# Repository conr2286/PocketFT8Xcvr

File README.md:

# Pocket FT8 Revisited
A derivative of Charles Hill's Palm-Sized Pocket FT8 Transceiver

# Attribution
* Copyright (C) 2025, James R Conrad (KQ7B), conr2286 *at* gmail *dot* com
* Copyright (C) 2021, Charles Hill (W5BAA), https://github.com/Rotron/Pocket-FT8 
* Si4735 Library developed by Ricardo Caritti: https://github.com/pu2clr/SI4735
* FT8 Decoding Library by Karlis Goba (YL3JG): https://github.com/kgoba/ft8_lib
* SN74ACT244 PA by Barb (WB2CBA), https://github.com/WB2CBA/DX-FT8-FT8-MULTIBAND-TABLET-TRANSCEIVER 
* Adafruit, PJRC and many Arduino libraries copyrighted by their respective authors

# Permissive MIT License (applies to most project files)
* Copyright (c) 2018 Kārlis Goba
* Copyright (C) 2019 Ricardo Lima Caratti
* Copyright (C) 2021, Charles Hill (W5BAA)
* Copyright (C) 2024, 2025 Jim Conrad (KQ7B)

Permission is hereby granted, free of charge, to any person obtaining a copy of this software and associated documentation files (the "Software"), to deal in the Software without restriction, including without limitation the rights to use, copy, modify, merge, publish, distribute, sublicense, and/or sell copies of the Software, and to permit persons to whom the Software is furnished to do so, subject to the following conditions:

The above copyright notice and this permission notice shall be included in all copies or substantial portions of the Software.

THE SOFTWARE IS PROVIDED "AS IS", WITHOUT WARRANTY OF ANY KIND, EXPRESS OR IMPLIED, INCLUDING BUT NOT LIMITED TO THE WARRANTIES OF MERCHANTABILITY, FITNESS FOR A PARTICULAR PURPOSE AND NONINFRINGEMENT. IN NO EVENT SHALL THE AUTHORS OR COPYRIGHT HOLDERS BE LIABLE FOR ANY CLAIM, DAMAGES OR OTHER LIABILITY, WHETHER IN AN ACTION OF CONTRACT, TORT OR OTHERWISE, ARISING FROM, OUT OF OR IN CONNECTION WITH THE SOFTWARE OR THE USE OR OTHER DEALINGS IN THE SOFTWARE.

# CopyLeft GPL License (applies to the SI5351 library)
* Copyright (C) 2015-2019 Jason Milldrum and Dana H. Myers

# Features
* Single band, FT8 Tranceiver
* Designed for 160-15 meters, tested on 40m
* Small Size, 4.0 X 2.8", 4-layer board
* Powered by a single 5V USB source (e.g. portable USB power block) delivering ~375 mA
* Si4735 SSB Receiver
* TCXO stabilized Si5351 Clock
* SN74ACT244 PA delivering ~250 mW on 40M (Tnx, Barb;)
* ADIF Contact Logging to SD card
* Adafruit 320 X 480 Resistive Color Touch Screen
* Optional Adafruit Ultimate GPS-derived location and UTC date/time
* RoboOp sequences FT8 QSOs somewhat akin to wsjtx

# DSP Audio Architecture
Decoding FT8 requires significant data storage and processing speed.  To optimize program storage and processing speed so the Teensy is not over taxed, the Teensy Audio Library has been modified to allow Analog to Digital conversion to be run at the rate of 6400 samples per second. This allows audio data processing to be done at 3200 Hz. The 3200 Hz audio processing with a 2048 FTT to process the received audio for FT8 decoding yields a bin spacing of 3.125 Hz.  For Teensy 4.1, the revised sample rate requires replacement of the core AudioStream.h file with the AudioStream6400.h file in the PocketFT8FW sketch folder.

The algorithms developed by Karlis Goba use the 3.125 Hz spaced FFT bins to be screened in both frequency and time so that errors in symbol frequency and time reception can be overcome to provide really great FT8 decoding. The end spacing of the FT8 algorithms is 6.25 Hz.

# Motivation and Related Projects
In the mid-60s, the ARRL Handbook published a receiver design known as the Junior Miser's Dream offering so much with so little.  Today, Charley Hill's concept for a self-contained FT8 transceiver, ideal for portable operation, again achieves so much with so little.  The entire transceiver fits in a small enclosure, powered by a USB power brick.  Pocket FT8 Revisited is a derivative of Charley's original concept.

Unlike the uSDX and related multi-mode designs, Pocket FT8 focuses entirely on FT8.  If you need CW, SSB, etc then Pocket FT8 is not for you.

Charley and Barb have progressed with another Pocket FT8 derivative, DX FT8, at https://github.com/WB2CBA/DX-FT8-FT8-MULTIBAND-TABLET-TRANSCEIVER, most notably replacing the SI4735 with a Tayloe receiver.

# Manifest
* BenchTests:  Arduino sketches for incremental tests of the hardware
* Bibliography:  "..shoulders of giants"
* Doc:  Minimalist user manual
* Enclosure:  STLs for 3D printing a plastic case for an older version (needs update)
* Examples:  Sample JSON configuration and ADIF log files
* Extras:  Modified Teensy AudioStream6400.h header (you *need* this)
* Investigations:  Code and simulations exploring technologies for this project
* Mfg:  BOM files for assembly.  V2.00 has been built; the current BOM awaits tariff issues.
* PocketFT8XcvrFW:  The transceiver firmware sources
* PocketFT8XcvrHW:  KiCad files for the PCB
* RFFilters:  Investigations into various filter designs
* Extras:  Contains Teensy AudioStream.h modified for 6400 samples/second.  You *need* this.
* Schematics:  PDFs of hardware schematics.  V2.00 matches V2.00 BOM.
* SpectralPurity:  Results of investigations into transmitter output using V2.00 hardware.

# Versions
* V1.00 PCB gerbers and pos files submitted to PCBWay.
* V1.10 Transmitter works.  Receiver occasionally decodes FT8 messages.  See Issue #23 on github.
* V2.00 Revised PCB moves the SI5351 and MCP342x to Wire1 to avoid I2C noise (Issue #23) hampering the SI4735
* V2.10 Implements GPS, ADIF logging and the RoboOp QSO sequencer.  Uses V2.00 hardware with patch wires for GPS connector.  The GPS is optional but *strongly* recommended.
* V3.00 continues with the same firmware, but the hardware eliminates the requirement for the PPS patch wire and adds an expansion connector to break-out a few GPIO signals.  The V3.00 board fabrication awaits a satisfactory tariff solution.

# Implementationi Notes
* The receiver is based upon the SI4735 chip offering a compact, low-power approach for most HF bands  Following up on a tip from the SI4735's application notes, the chip was found to be extremely sensitive to noise from other I2C traffic on the same bus as the SI4735.  The V2.00 boards address this issue by moving the touchscreen (MCP342X) and SI5351 traffic from the Wire to the Wire1 I2C bus, isolating the SI4735 on Wire.  Likewise, the V2.00 boards pay more attention to signal routing adjacent to noise-sensitive circuitry.
* Many clock designs use a TCXO driving one of the SI5351's XTAL pins and often in conflict with the SI5351 application notes recommendations.  Many designers have commented (not of one voice;) on this approach.  Following up on a now-misplaced tip re. phase noise, this design employs a low jitter TCXO driving the SI5351's CLKIN pin.  Following up on yet another misplaced tip regarding the SI5351's phase noise when driving heavy loads, the V2.00 boards buffer the XCLK signal from the SI5351.  All this may be overkill but it was easy to implement.
* The V2.00 boards and the original Pocket FT8 project use an external MCP342x ADC to poll the touchscreen.  With a non-blocking ADC library, the Teensy 4.1 could likely use the second internal ADC but this idea has not yet been tested (it can be achieved using a patch to the V2.00 boards).  Alternative approaches include using a touchscreen controller.  These are considered for a future V4.00.
* The V1.10 LP filter lacked rejection of received signals below the operating frequency.  Spectral investigations into the found surprisingly strong signals in the 500..7000 kHz range having the potential to limit the receiver's performance.  The V2.00 board filter plugins offer a chance to explore a bandpass design to protect the receiver's front end.  Suitable bandpass filters have been modeled but not yet been tested.
* The V2.00 boards support the Adafruit Ultimate GPS Breakout board.  The firmware supports using the PPS digital interrupt signal to determine when the GPS acquires a fix; however, the V2.00 PCB requires a patch wire to connect the PPS pin to Teensy Digital Pin 2, and the GPS connector has the PPS pin in an awkward location for a ribbon cable.  This will hopefull be fixed in the V3.00 hardware when tariffs permit.  The patch is easy to solder and I strongly recommend it.

# Boards and Parts Availability
Pocket FT8 Revisited is not a kit.  If you seek a kit-like experience, check-out QRP Labs, the uSDX follow-ons, or the DX FT8 kit because Pocket FT8 construction requires some engineering skills and tools including KiCAD, the Arduino IDE, and Visual Studio Code with the PlatformIO extensions.  This project is more about homebrewing than operating.  That said, sometimes I have spare boards for one version or another.

# Building the Firmware
1. Install Arduino 2.X IDE (the BenchTests still require the Arduino IDE, sorry)
2. Using Arduino 2.X, install support for the Teensy 4.1 board
3. Install Visual Studio Code and PlatformIO
4. Using PlatformIO, install support for the Teensy 4.1 platform
5. Using PlatformIO, install support for the required libraries (documented in the PocketFT8XcvrFW folder)
6. Copy Extras/AudioStream6400.h into
 .../Library/Arduino15/packages/teensy/hardware/avr/1.59.0/cores/teens4 asArduinoStream.h --- This file redefines AUDIO_SAMPLE_RATE_EXACT enabling Teensy 4.1 to operate the audio stream at 6400 samples/second (required).  You absolutely *must* do this; PocketFT8XcvrFW.cpp will not execute if you forget.
7. Build the firmware with PlatformIO.  The project src files build without warnings; library files... not so much.

# Hardware Notes
Pocket FT8 Revisited was designed with KiCAD, and the V2.00 PCBs were fabbed and the SMD assembled by PCBWay.  There are two boards, the main board (PocketFT8XcvrHW) and a daughter board for the filter (RFFilters).  I used the 5Pole40MLPFilter in the SpectralPurity test.  The V3.00 boards are designed and checked but await a satisfactory tariff solution for fabrication and assembly.

# Building the Hardware
1. Attach the Teensy 4.1 MPU to the board using *low profile* headers.
2. Attach the Adafruit resistive 320x480 touchscreen with high profile headers (so the display clears the MPU)
3. Construct a suitable filter (e.g. 5-pole Chebyshev) for your chosen band of operation and solder it into the FL1 spot.  The RFFilters folder contains a KiCAD design for the filter daughter board.
4. Hand solder SMD CR2032 battery holder to reverse side of PCB and install battery (before powering-up the Teensy).  T
5. Hand solder THT red XMIT LED
6. Wind THT T1 (10T bifilar #26 on FT37-43 core) and install
7. Install right angle header for GPS.  Hand solder a PPS patch wire from the GPS connector to the MCU as described above.
8. Hand solder the SMD SMA antenna socket to the board
9. Smoke test with wall wart USB supply (not your expensive computer;)
10. Build and execute each of the BenchTests (with Arduino IDE 2.00) in numerical order to individually check-out the circuit subsystems.

# Putting Pocket FT8 Revisited On-the-Air
1. Create an SD file, CONFIG.JSON, to configure the Pocket FT8 for your station (see the sample file in Examples).  The required parameters are, callsign and frequency.  If you don't have a GPS, you'll also need location.  Install the SD card in Teensy (*not* in the Adafruit display which also has an SD slot).
2. If you are using a GPS, connect it now.
3. Connect an antenna 
4. Connect your host computer and load your firmware

# Usage
## CONFIG.JSON
During setup(), the rig reads the config.json file, if available, from the Teensy SD card.  The SD card and configuration file are required to enable the transmitter.  See the example config file in the Examples folder.  The important configuration parameters include:
* callsign      Station callsign.  *Required* to enable the transmitter.
* frequency     Operating frequency in kHz (default is 7074).
* locator       Four letter Maidenhead grid square (Required if no GPS).
* enableAVC     Enable/disable SI4735 AVC (default is enabled).
* qsoTimeout    Seconds the QSO Sequencer will retransmit a msg without receiving a usable response from remote station (default is 180)

## GPS
If available, the rig will use the current UTC date, time and location (Maidenhead grid square) from an attached GPS.  The V2.00 hardware requires a patch wire to connect the GPS PPS connector pin to Teensy digital pin 2.  The firmware monitors PPS interrupts and begins using the UTC time and location only when/if the GPS acquires a satellite fix.  
Without a GPS fix, the firmware uses the date/time from the battery-backed Teensy Real Time Clock (RTC) and displays that date/time in yellow.  After a fix is obtained, the date/time displays in green.  The GPS is not required but *greatly* facilitates UTC logging and accurate synchronization with FT8 timeslots.

## Logging
Pocket FT8 logs successful contacts to an ADIF file on the Teensy SD disk.  The date/time are recorded in UTC if the rig has acquired a GPS fix.  If the rig has never had a GPS fix, the date/time come from the boot loader and the computer that installed the firmware --- that may work for FT8 but the UTC date/time will be incorrect in the ADIF log.  You really do want the GPS.  The logging software considers a contact successful when the rig obtains the remote station's callsign and signal report (yes, that's a little more severe than required by ARRL's LoTW).  Without a GPS, the grid locator can be obtained from the configuration file.

## Robo-Op
Pocket FT8 firmware includes a "RoboOp" "sequencer somewhat akin (or ajar...;) to those used in wsjtx and DX FT8.  The sequencer conducts a standard FT8 QSO initiated with your station's CQ, or with your reply to a station calling CQ.  The sequencer automagically coordinates its transmissions with those of the remote station to avoid "doubling" (transmitting in the same timeslot as the remote transmission).  In most cases, the sequencer prepares a reply during the FT8 "dwell" time (between timeslots) and can transmit in the very next timeslot.  If not... well... it will wait for an appriopriate even/odd timeslot.
The sequencer is implemented as a giant state machine that attempts to make the best of difficult conditions/responses to complete a troubled QSO.  The sequencer has a configurable QSO Timeout feature to abort a run-on QSO (including CQ) arising from QRM, QRN, or a QRT/QLF remote station.  As with most large state machines... the code is difficult to follow, but is mitigated with an abundance of comments that attempt to explain what's happening in the various event handlers and their actions.

## CQ Button
The CQ button directs RoboOp to begin calling CQ in the next FT8 timeslot.  RoboOp will continue calling CQ until either a response is received, a timeout occurs, the operator toggles the CQ button, or clicks the ABort button.

## TU Button
The TUne button transmits a dead carrier at the CONFIG.JSON specified operating frequency.  Toggling the TUne button or clicking ABort drops the carrier.

## AB Button
The ABort button aborts a transmission in-progress.

## TX Button
The TX button directs RoboOp to respond to the first received CQ message.  Unless CONFIG.JSON has configured otherwise, RoboOp ignores recent duplicates already in the log.  Toggling the TX button or the completion of a QSO disables the TX mode auto-responses.

## M0, M1 and M2 Buttons
These buttons transmit a free-text FT8 message specified in CONFIG.JSON.

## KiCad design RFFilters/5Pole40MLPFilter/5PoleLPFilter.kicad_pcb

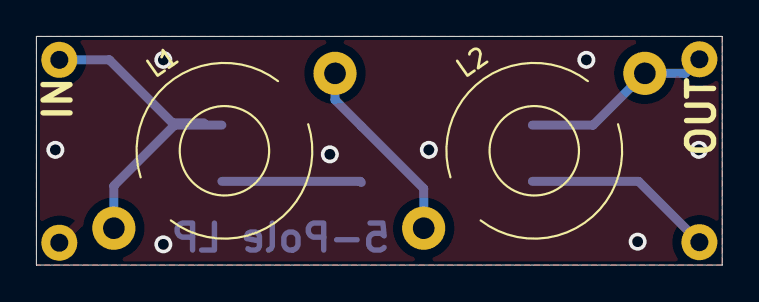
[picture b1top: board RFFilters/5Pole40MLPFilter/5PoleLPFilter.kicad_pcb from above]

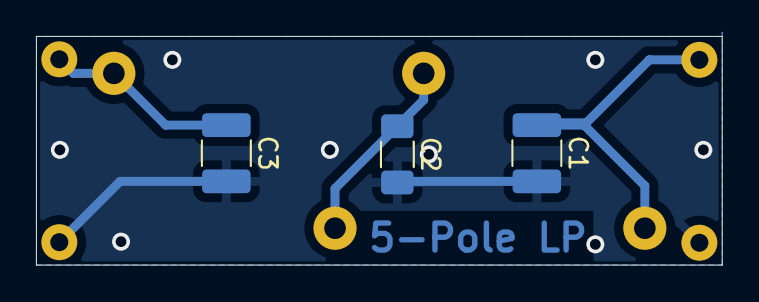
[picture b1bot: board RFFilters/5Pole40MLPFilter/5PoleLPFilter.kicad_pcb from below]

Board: 2 copper layers, 38.1 x 12.7 mm, 6 parts (3 on the bottom side), 2 nets.

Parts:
C1, C3: 1000pF; C_1210_3225Metric_Pad1.33x2.70mm_HandSolder
C2: 1300pf; C_1206_3216Metric_Pad1.33x1.80mm_HandSolder
J1: FilterConn02
L1, L2: 1.2uH; L_Toroid_Horizontal_D9.5mm_P15.00mm_Diameter10-5mm_Amidon-T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

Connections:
/Mid: C2.1, L1.2, L2.1
GND: C1.2, C2.2, C3.2, J1.2

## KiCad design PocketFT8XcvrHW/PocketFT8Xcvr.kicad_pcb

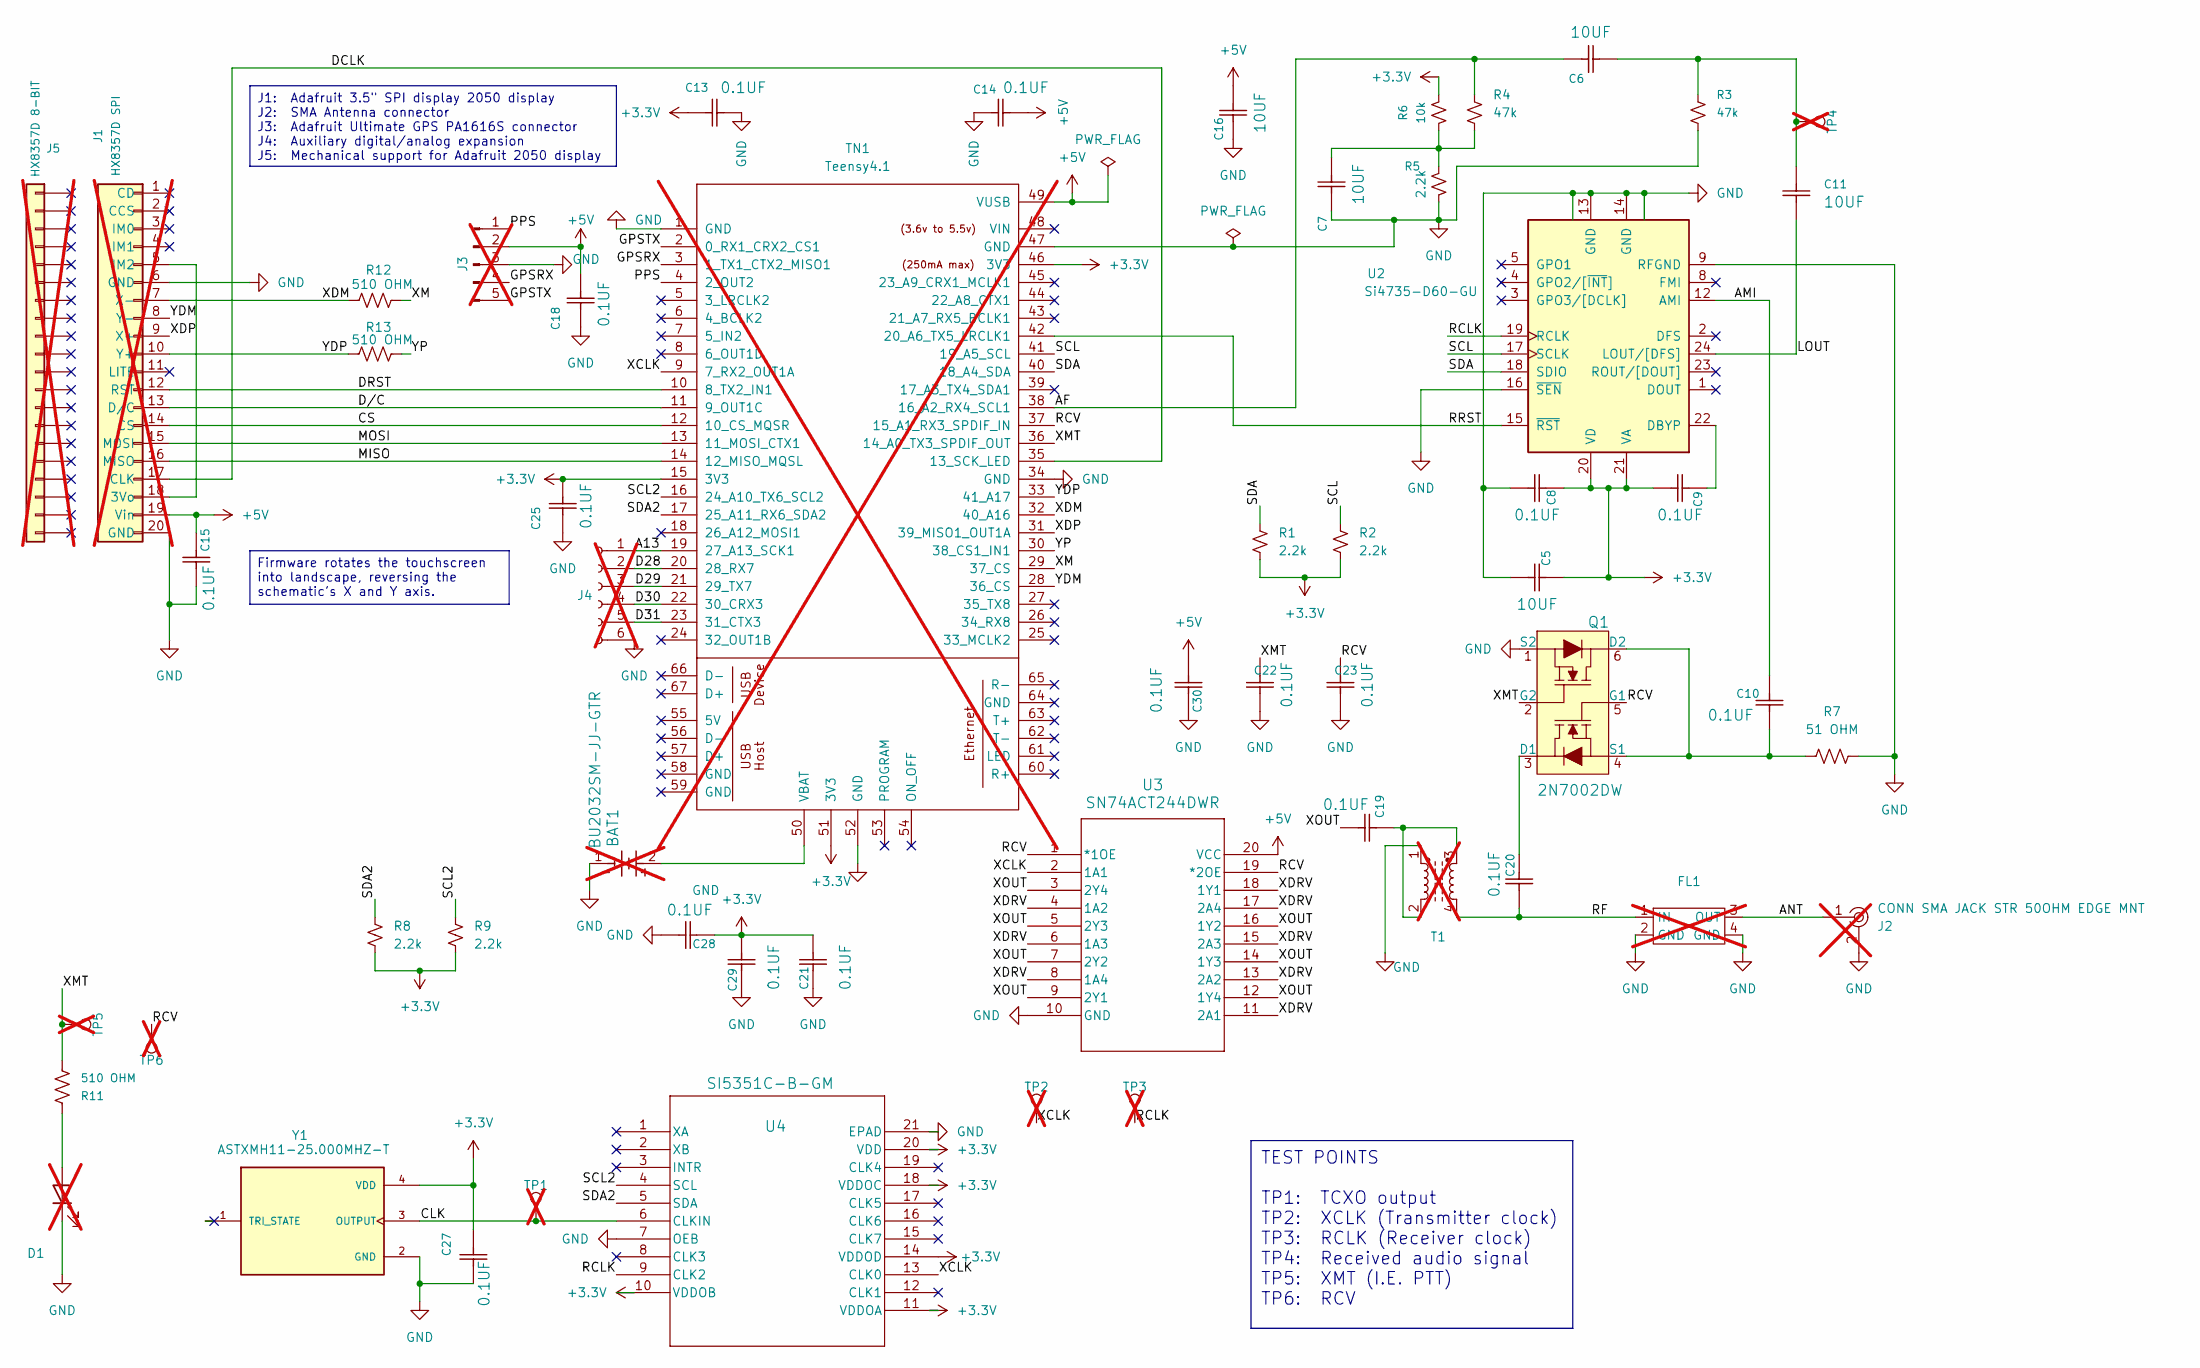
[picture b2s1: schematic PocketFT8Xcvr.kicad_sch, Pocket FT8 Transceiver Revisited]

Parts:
BAT1: BU2032SM-JJ-GTR; BU2032SM-JJ-GTR_MPD; Mfg Part # BU2032SM-JJ-GTR; not fitted
C5: 10UF; C_0805_2012Metric; Voltage 16V; Tolerance 10%; Mfg Part # C0805C106K4PAC7800
C6, C7, C11, C16: 10UF; C_0805_2012Metric; Voltage 6.3V; Tolerance 20%; Mfg Part # C0805C106K4PAC7800
C8, C9, C10, C13, C14, C15, C18, C19, C20, C21, C22, C23, C25, C27, C28, C29, C30: 0.1UF; C_0603_1608Metric; Voltage 16V; Tolerance 10%; Mfg Part # C0603C104K4RACTU
D1: XMIT; LED_D5.0mm; not fitted
FL1: PluginFilter; not fitted
J1: HX8357D SPI; PinHeader_1x20_P2.54mm_Vertical; not fitted
J2: CONN SMA JACK STR 50OHM EDGE MNT; RF_SMA_BoardEdge_142-0701-801; MPN 732511153; Digi-Key_PN J502-ND; not fitted
J3: B5B-XH-A_LF__SN_; PinHeader_1x5_P2.5mm_Drill1.1mm; MPN B5B-XH-A(LF)(SN); Digi-Key_PN 455-2270-ND; not fitted
J4: Conn_01x06_Socket; 1x06; not fitted
J5: HX8357D 8-BIT; PinHeader_1x20_P2.54mm_Vertical; not fitted
Q1: 2N7002DW; SOT-363; Mfg Part # 2N7002DW; Digi-Key_PN 2N7002DWCT-ND
R1, R2, R5, R8, R9: 2.2k; R_0603_1608Metric; Mfg Part # RC0603JR-132K2L
R3, R4: 47k; R_0603_1608Metric; Mfg Part # RC0603JR-0747KL; LCSC Part # C127447
R6: 10k; R_0603_1608Metric; Mfg Part # AF0603JR-0710KL; LCSC Part # C99198
R7: 51 OHM; R_0603_1608Metric; Mfg Part # RC0603JR-0751RL
R11, R12, R13: 510 OHM; R_0603_1608Metric; MFG PART # RC0603JR-07510RL
T1: L_Ferrite_Coupled; L_Toroid_Vertical_BIFILAR; not fitted
TN1: Teensy4.1; Teensy41; not fitted
TP1, TP2, TP3, TP4, TP5, TP6: PTH; 1x01; not fitted
U2: Si4735-D60-GU; SSOP-24_3.9x8.7mm_P0.635mm; Mfg Part # SI4735-D60-GU
U3: SN74ACT244DWR; DW20; Mfg Part # SN74ACT244DWR
U4: SI5351C-B-GM; QFN20_4X4_SKY; Mfg Part # SI5351C-B-GM
Y1: ASTXMH11-25.000MHZ-T; XTAL_ASTX-H11-25.000MHZ-T; PARTREV 05.13.15

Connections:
+3.3V: C5.2, C8.2, C9.1, C13.1, C21.2, C25.1, C27.2, C28.1, C29.2, R1.1, R2.1, R6.1, R8.1, R9.1, TN1.15 (3V3), TN1.46 (3V3), TN1.51 (3V3), U2.20 (VD), U2.21 (VA), U4.10 (VDDOB), U4.11 (VDDOA), U4.14 (VDDOD), U4.18 (VDDOC), U4.20 (VDD), Y1.4 (VDD)
+5V: C14.2, C15.2, C16.2, C18.2, C30.2, J1.19 (Vin), J3.2, TN1.49 (VUSB), U3.20 (VCC)
/A13: J4.1, TN1.19 (27_A13_SCK1)
/AF: C6.2, R4.1, TN1.38 (16_A2_RX4_SCL1)
/AMI: C10.2, U2.12 (AMI)
/ANT: FL1.3 (OUT), J2.1
/CLK: TP1.1, U4.6 (CLKIN), Y1.3 (OUTPUT)
/CS: J1.14 (CS), TN1.12 (10_CS_MQSR)
/D28: J4.2, TN1.20 (28_RX7)
/D29: J4.3, TN1.21 (29_TX7)
/D30: J4.4, TN1.22 (30_CRX3)
/D31: J4.5, TN1.23 (31_CTX3)
/DCLK: J1.17 (CLK), TN1.35 (13_SCK_LED)
/DRST: J1.12 (RST), TN1.10 (8_TX2_IN1)
/D/C: J1.13 (D/C), TN1.11 (9_OUT1C)
/GPSRX: J3.4, TN1.3 (1_TX1_CTX2_MISO1)
/GPSTX: J3.5, TN1.2 (0_RX1_CRX2_CS1)
/LOUT: C11.1, U2.24 (LOUT/[DFS])
/MISO: J1.16 (MISO), TN1.14 (12_MISO_MQSL)
/MOSI: J1.15 (MOSI), TN1.13 (11_MOSI_CTX1)
/PPS: J3.1, TN1.4 (2_OUT2)
/RCLK: TP3.1, U2.19 (RCLK), U4.9 (CLK2)
/RCV: C23.2, Q1.5 (G1), TN1.37 (15_A1_RX3_SPDIF_IN), TP6.1, U3.1 (*1OE), U3.19 (*2OE)
/RF: C20.2, FL1.1 (IN), T1.4
/RRST: TN1.42 (20_A6_TX5_LRCLK1), U2.15 (~RST)
/SCL: R2.2, TN1.41 (19_A5_SCL), U2.17 (SCLK)
/SCL2: R9.2, TN1.16 (24_A10_TX6_SCL2), U4.4 (SCL)
/SDA: R1.2, TN1.40 (18_A4_SDA), U2.18 (SDIO)
/SDA2: R8.2, TN1.17 (25_A11_RX6_SDA2), U4.5 (SDA)
/XCLK: TN1.9 (7_RX2_OUT1A), TP2.1, U3.2 (1A1), U4.13 (CLK0)
/XDM: J1.7 (X-), R12.1, TN1.32 (40_A16)
/XDP: J1.9 (X+), TN1.31 (39_MISO1_OUT1A)
/XDRV: U3.4 (1A2), U3.6 (1A3), U3.8 (1A4), U3.11 (2A1), U3.13 (2A2), U3.15 (2A3), U3.17 (2A4), U3.18 (1Y1)
/XM: R12.2, TN1.29 (37_CS)
/XMT: C22.2, Q1.2 (G2), R11.2, TN1.36 (14_A0_TX3_SPDIF_OUT), TP5.1
/XOUT: C19.1, U3.3 (2Y4), U3.5 (2Y3), U3.7 (2Y2), U3.9 (2Y1), U3.12 (1Y4), U3.14 (1Y3), U3.16 (1Y2)
/YDM: J1.8 (Y-), TN1.28 (36_CS)
/YDP: J1.10 (Y+), R13.1, TN1.33 (41_A17)
/YP: R13.2, TN1.30 (38_CS1_IN1)
GND: BAT1.1, C5.1, C7.1, C8.1, C13.2, C14.1, C15.1, C16.1, C18.1, C21.1, C22.1, C23.1, C25.2, C27.1, C28.2, C29.1, C30.1, D1.1 (K), FL1.2 (GND), FL1.4 (GND), J1.6 (GND), J1.20 (GND), J2.2, J3.3, J4.6, Q1.1 (S2), R3.2, R5.2, R7.1, T1.1, TN1.1 (GND), TN1.34 (GND), TN1.47 (GND), TN1.52 (GND), U2.9 (RFGND), U2.10 (NC), U2.11 (NC), U2.13 (GND), U2.14 (GND), U2.16 (~SEN), U3.10 (GND), U4.7 (OEB), U4.21 (EPAD), Y1.2 (GND)
unnamed: C7.2, R4.2, R5.1, R6.2
unnamed: C6.1, C11.2, R3.1, TP4.1
unnamed: C19.2, T1.2, T1.3
unnamed: D1.2 (A), R11.1
unnamed: J1.5 (IM2), J1.18 (3Vo)
unnamed: C20.1, Q1.3 (D1)
unnamed: C10.1, Q1.4 (S1), Q1.6 (D2), R7.2
unnamed: BAT1.2, TN1.50 (VBAT)
unnamed: C9.2, U2.22 (DBYP)

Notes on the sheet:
TEST POINTS TP1: TCXO output TP2: XCLK (Transmitter clock) TP3: RCLK (Receiver clock) TP4: Received audio signal TP5: XMT (I.E. PTT) TP6: RCV
Firmware rotates the touchscreen into landscape, reversing the schematic's X and Y axis.
J1: Adafruit 3.5" SPI display 2050 display J2: SMA Antenna connector J3: Adafruit Ultimate GPS PA1616S connector J4: Auxiliary digital/analog expansion J5: Mechanical support for Adafruit 2050 display

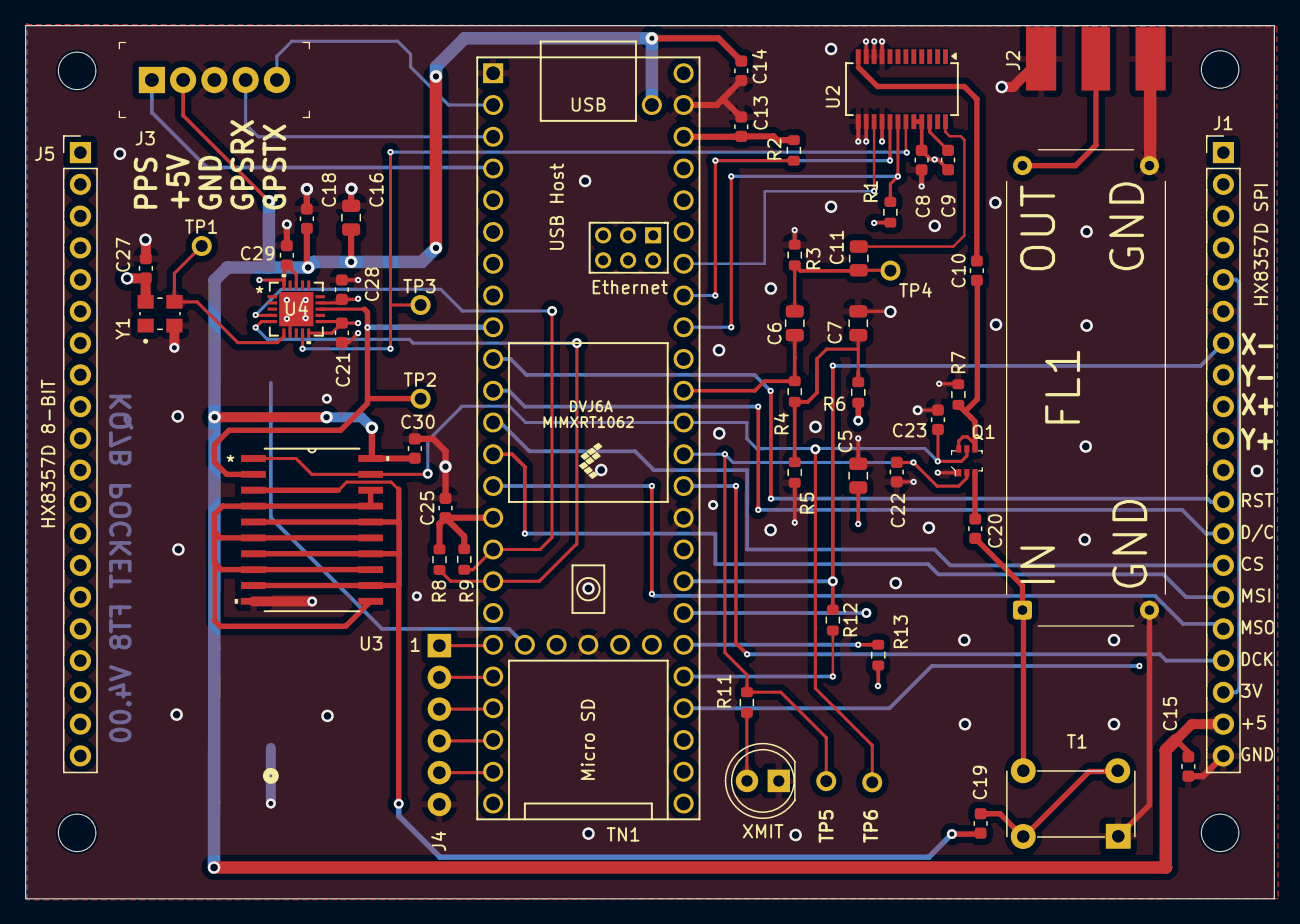
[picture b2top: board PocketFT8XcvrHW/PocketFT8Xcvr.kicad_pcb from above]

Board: 4 copper layers, 99.9 x 69.9 mm, 55 parts (1 on the bottom side), 49 nets.

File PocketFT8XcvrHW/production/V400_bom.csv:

Designator,Footprint,Quantity,Value,LCSC Part #
"C10, C13, C14, C15, C18, C19, C20, C21, C22, C23, C25, C27, C28, C29, C30, C8, C9",0603,17,0.1UF,
"C11, C16, C5, C6, C7",0805,5,10UF,
Q1,SOT-363,1,2N7002DW,
"R1, R2, R8, R9",0603,4,2.0K,
R11,0603,1,510 Ohm,
"R12, R13",0603,2,510,
"R3, R4",0603,2,47K,
R5,0603,1,2.2K,
R6,0603,1,10k,
R7,0603,1,51 OHM,
U2,SSOP-24_3.9x8.7mm_P0.635mm,1,Si4735-D60-GU,
U3,DW20,1,SN74ACT244DWR,
U4,QFN20_4X4_SKY,1,SI5351C-B-GM,
Y1,XTAL_ASTX-H11-25.000MHZ-T,1,ASTXMH11-25.000MHZ-T,

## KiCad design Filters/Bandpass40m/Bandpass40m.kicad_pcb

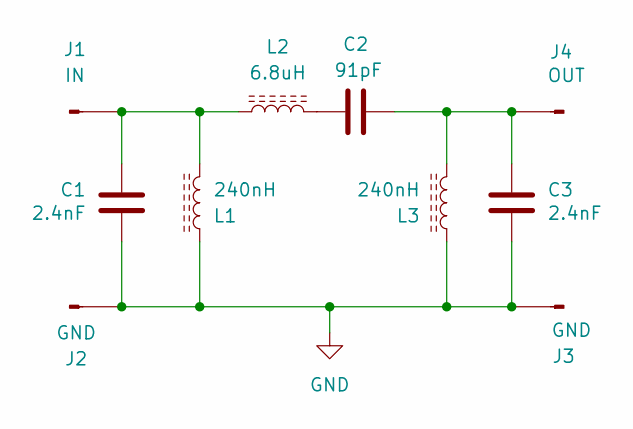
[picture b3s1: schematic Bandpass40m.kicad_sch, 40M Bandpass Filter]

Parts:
C1, C3: 2.4nF; C_0603_1608Metric_Pad1.08x0.95mm_HandSolder; MPN GCM1885C1H242FA16J
C2: 91pF; C_0603_1608Metric_Pad1.08x0.95mm_HandSolder; MPN GCM1885C2A910FA16D
J1: IN; PinHeader_1x01_P2.00mm_Vertical
J2, J3: GND; PinHeader_1x01_P2.00mm_Vertical
J4: OUT; PinHeader_1x01_P2.00mm_Vertical
L1, L3: 240nH; Inductor_THT_Horizontal_T37
L2: 6.8uH; Inductor_THT_Horizontal_T37

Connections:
GND: C1.2, C3.2, J2.1, J3.1, L1.2, L3.1
unnamed: C2.1, L2.2
unnamed: C1.1, J1.1, L1.1, L2.1
unnamed: C2.2, C3.1, J4.1, L3.2

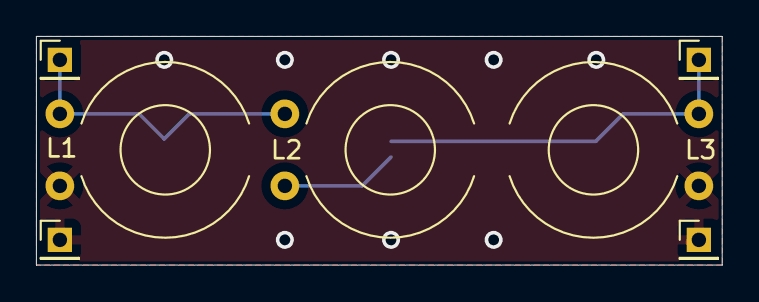
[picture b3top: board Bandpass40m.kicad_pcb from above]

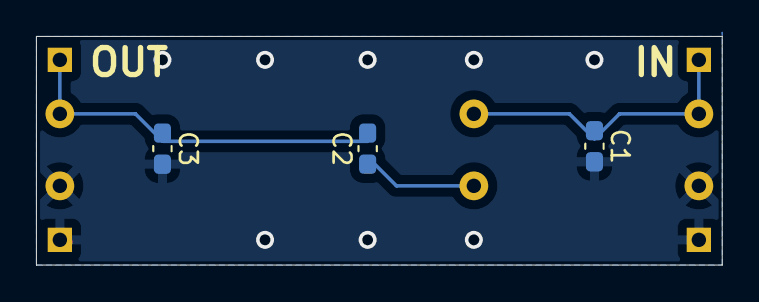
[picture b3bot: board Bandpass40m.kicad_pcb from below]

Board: 2 copper layers, 38.1 x 12.7 mm, 10 parts (3 on the bottom side), 4 nets.

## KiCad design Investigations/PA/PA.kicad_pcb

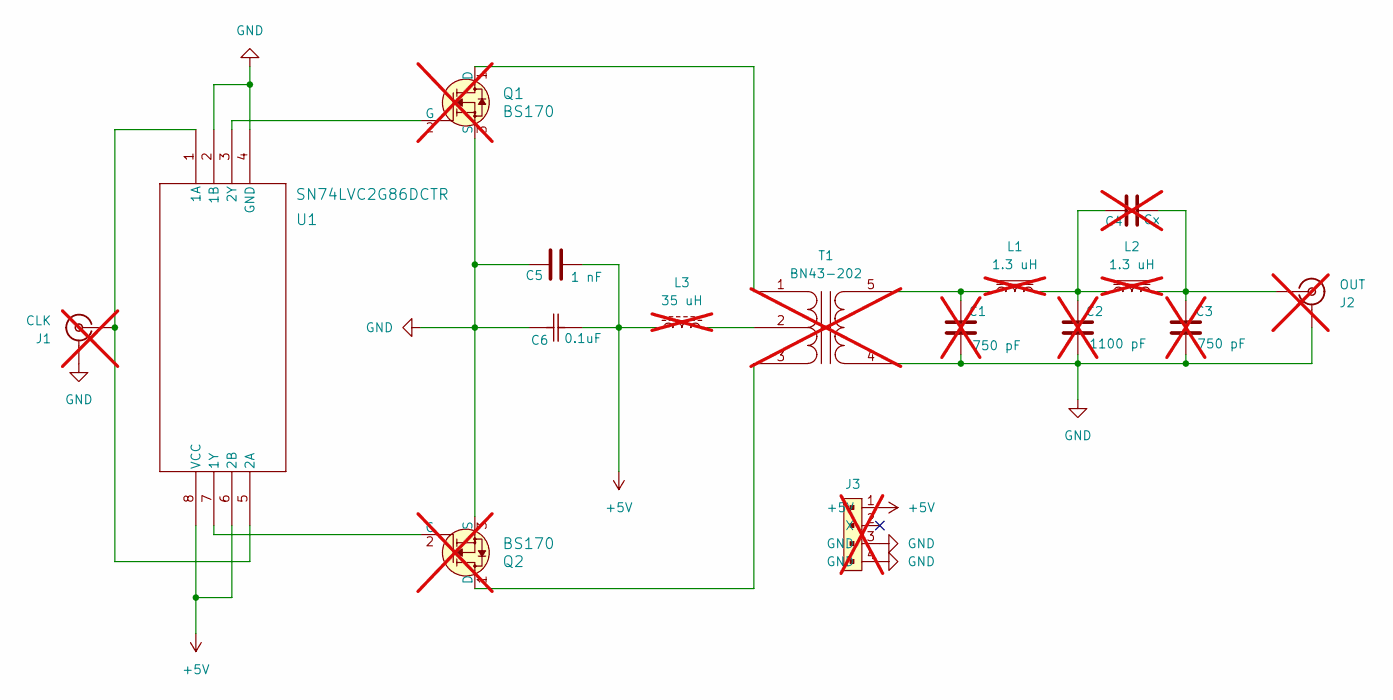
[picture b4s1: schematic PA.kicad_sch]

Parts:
C1, C3: 750 pF; 1210; Voltage 1kV; Tolerance 100%; not fitted
C2: 1100 pF; 1210; Voltage 1kV; Tolerance 100%; not fitted
C4: Cx; 1210; Voltage 1kV; Tolerance 100%; not fitted
C5: 1 nF; 1210; Voltage 50V; Tolerance 5%
C6: 0.1uF; 1210; Voltage 50V; Tolerance 5%; Mfg Part # C1210C104J5GAC7800
J1: CLK; SMA_Edge; not fitted
J2: OUT; SMA_Edge; not fitted
J3: 0022232041; PinHeader_1x4_P2.54mm_Drill1.02mm; MPN 0022232041; Digi-Key_PN WM4202-ND; not fitted
L1, L2: 1.3 uH; L_Toroid_Vertical_L13.0mm_W6.5mm_P5.60mm; not fitted
L3: 35 uH; L_Toroid_Vertical_L14.0mm_W5.6mm_P5.30mm_Bourns_5700; not fitted
Q1, Q2: BS170; TO-92-3; MPN BS170; Digi-Key_PN BS170-ND; not fitted
T1: BN43-202; not fitted
U1: SN74LVC2G86DCTR; DCT8_TEX

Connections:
+5V: C5.2, C6.1, J3.1 (+5V), L3.1, U1.6 (2B), U1.8 (VCC)
GND: C1.2, C2.2, C3.2, C5.1, C6.2, J1.2 (Ext), J2.2 (Ext), J3.3 (GND), J3.4 (GND), Q1.3 (S), Q2.3 (S), T1.4 (S1), U1.2 (1B), U1.4 (GND)
unnamed: C2.1, C4.1, L1.2, L2.1
unnamed: J1.1 (In), U1.1 (1A), U1.5 (2A)
unnamed: C3.1, C4.2, J2.1 (out), L2.2
unnamed: Q1.1 (D), T1.1 (PR1)
unnamed: Q1.2 (G), U1.3 (2Y)
unnamed: Q2.1 (D), T1.3 (PR2)
unnamed: Q2.2 (G), U1.7 (1Y)
unnamed: L3.2, T1.2 (PM)
unnamed: C1.1, L1.1, T1.5 (S2)

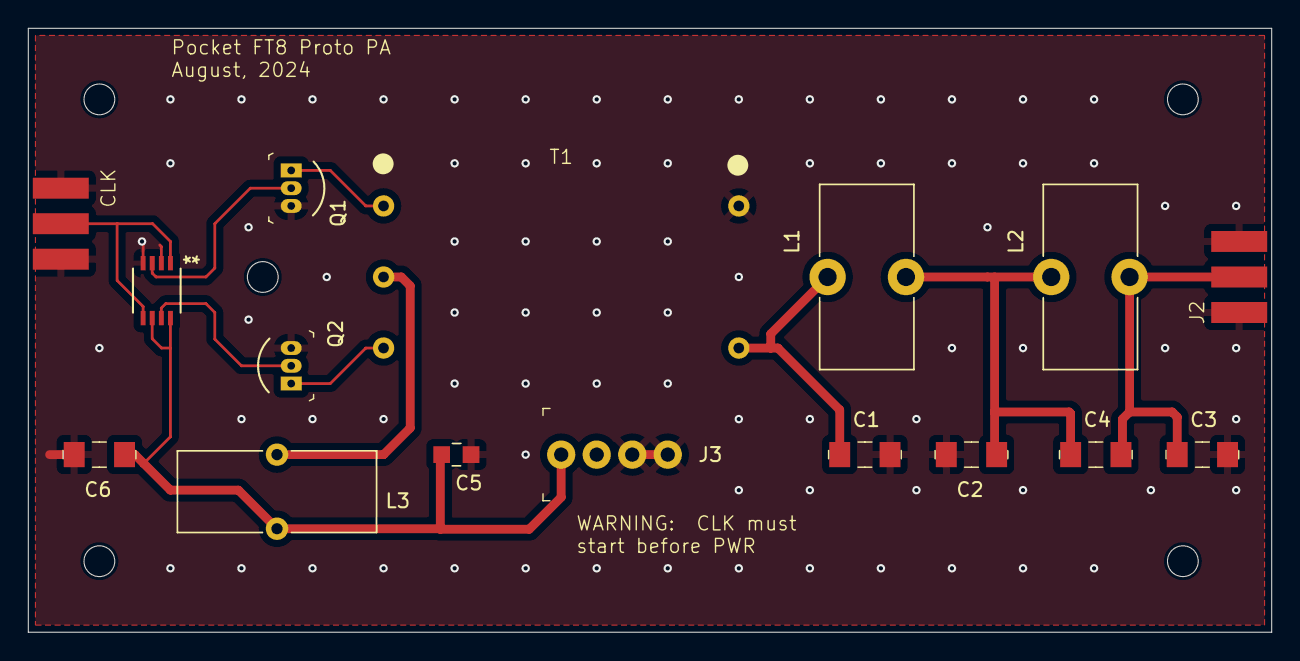
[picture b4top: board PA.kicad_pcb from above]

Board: 2 copper layers, 88.9 x 43.2 mm, 16 parts (0 on the bottom side), 11 nets.

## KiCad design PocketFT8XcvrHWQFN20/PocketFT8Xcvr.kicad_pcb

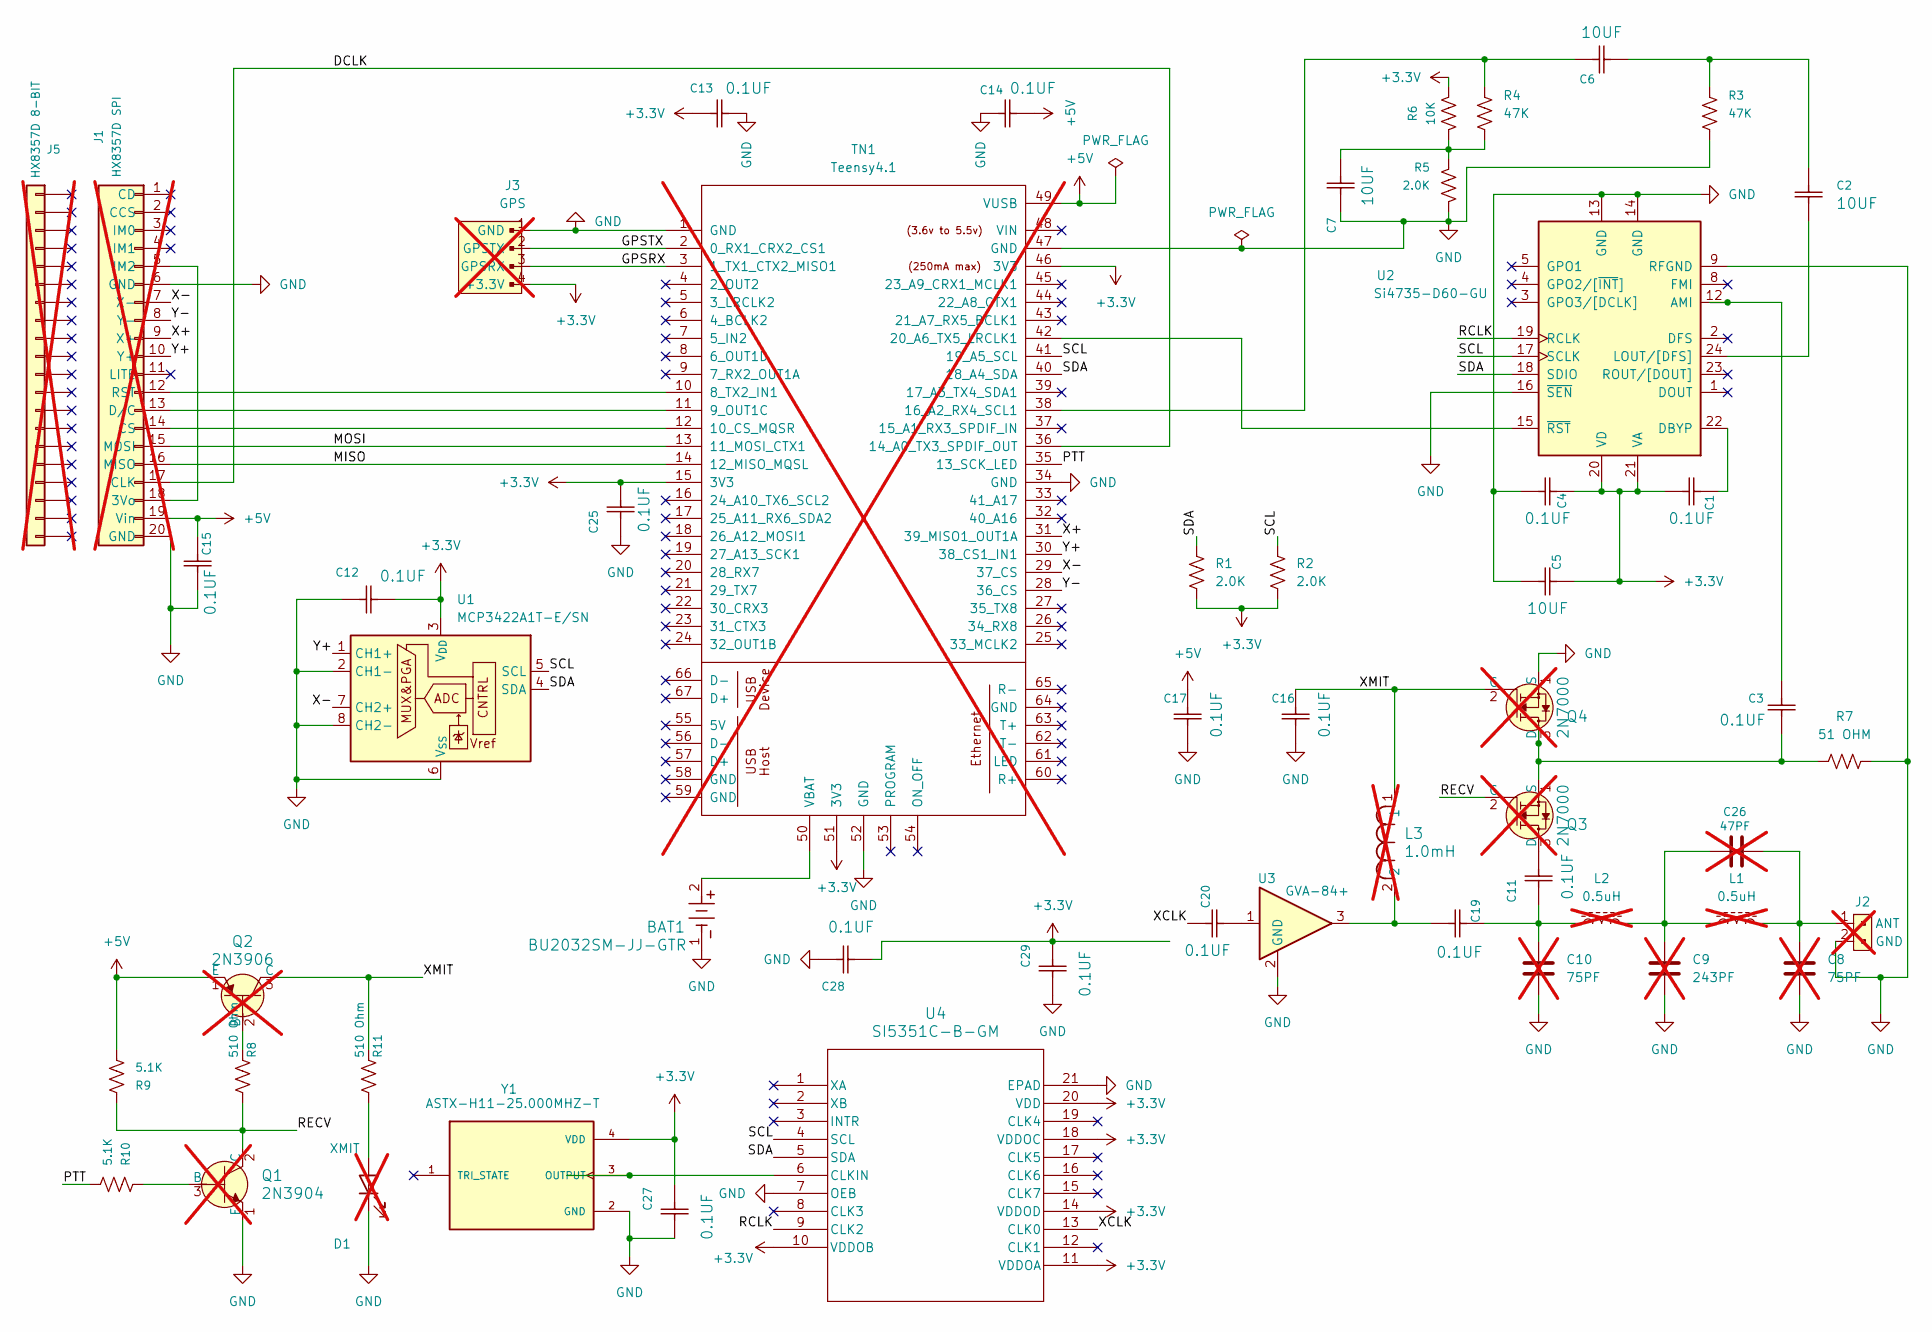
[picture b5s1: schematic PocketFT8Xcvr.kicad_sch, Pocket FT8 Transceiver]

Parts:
BAT1: BU2032SM-JJ-GTR; BU2032SM-JJ-GTR_MPD; Mfg Part # BU2032SM-JJ-GTR
C1, C3, C4, C11, C12, C13, C14, C15, C16, C17, C19, C20, C25, C27, C28, C29: 0.1UF; C_0603_1608Metric; Voltage 16V; Tolerance 10%; Mfg Part # C0603C104K4RAC7867
C2, C6, C7: 10UF; C_0805_2012Metric; Voltage 6.3V; Tolerance 20%; Mfg Part # C0805C106K4PAC7800
C5: 10UF; C_0805_2012Metric; Voltage 16V; Tolerance 10%; Mfg Part # C0805C106K4PAC7800
C8, C10: 75PF; C_0805_2012Metric; not fitted
C9: 243PF; C_0805_2012Metric; not fitted
C26: 47PF; C_0805_2012Metric; Voltage 100v; Tolerance 1%; not fitted
D1: XMIT; LED_D5.0mm; not fitted
J1: HX8357D SPI; PinHeader_1x20_P2.54mm_Vertical; not fitted
J2: 22-23-2021; PinHeader_1x2_P2.54mm_Drill1.02mm; MPN 22-23-2021; Digi-Key_PN WM4200-ND; not fitted
J3: GPS; PinHeader_1x4_P2.54mm_Drill1.02mm; MPN 0022232041; Digi-Key_PN WM4202-ND; not fitted
J5: HX8357D 8-BIT; PinHeader_1x20_P2.54mm_Vertical; not fitted
L1, L2: 0.5uH; L_Toroid_Vertical_L10.0mm_W5.0mm_P5.08mm; not fitted
L3: 1.0mH; IND_BOURNS_RLB9012; Mfg Part # RLB9012-102KL; Digi-Key_PN RLB9012-102KL-N; not fitted
Q1: 2N3904; TO-92-3; Mfg Part # 2N3904; Digi-Key_PN 2N3904CS-ND; not fitted
Q2: 2N3906; TO-92-3; Mfg Part # 2N3906; Digi-Key_PN 2N3906CS-ND; not fitted
Q3: 2N7000; TO-92-3; Mfg Part # 2N7000; Digi-Key_PN 2N7000FS-ND; not fitted
Q4: 2N7000; TO-92-3; MPN 2N7000; Digi-Key_PN 2N7000FS-ND; not fitted
R1, R2, R5: 2.0K; R_0603_1608Metric; Mfg Part # RC0603JR-072KL
R3, R4: 47K; R_0603_1608Metric; Mfg Part # RC0603JR-0747KL
R6: 10K; R_0603_1608Metric; Mfg Part # RC0603JR-0710KL
R7: 51 OHM; R_0603_1608Metric; Mfg Part # RC1210JR-0751RL
R8, R11: 510 Ohm; R_0603_1608Metric; Mfg Part # RC0603JR-07510RL
R9, R10: 5.1K; R_0603_1608Metric; Mfg Part # RC0603JR-075K1L
TN1: Teensy4.1; Teensy41; not fitted
U1: MCP3422A1T-E/SN; SOIC-8_3.9x4.9mm_P1.27mm; Mfg Part # MCP3422A1T-E/SN
U2: Si4735-D60-GU; SSOP-24_3.9x8.7mm_P0.635mm; Mfg Part # SI4735-D60-GU
U3: GVA-84+; SOT-89-3_Handsoldering; Mfg Part # GVA-84+
U4: SI5351C-B-GM; QFN20_4X4_SKY; Mfg Part # SI5351C-B-GM
Y1: ASTX-H11-25.000MHZ-T; XTAL_ASTX-H11-25.000MHZ-T; PARTREV 05.13.15

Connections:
+3.3V: C1.1, C4.2, C5.2, C12.1, C13.1, C25.1, C27.2, C28.1, C29.2, J3.4 (+3.3V), R1.2, R2.2, R6.2, TN1.15 (3V3), TN1.46 (3V3), TN1.51 (3V3), U1.3 (V_{DD}), U2.20 (VD), U2.21 (VA), U4.10 (VDDOB), U4.11 (VDDOA), U4.14 (VDDOD), U4.18 (VDDOC), U4.20 (VDD), Y1.4 (VDD)
+5V: C14.2, C15.2, C17.2, J1.19 (Vin), Q2.1 (E), R9.2, TN1.49 (VUSB)
/DCLK: J1.17 (CLK), TN1.36 (14_A0_TX3_SPDIF_OUT)
/GPSRX: J3.3 (GPSRX), TN1.3 (1_TX1_CTX2_MISO1)
/GPSTX: J3.2 (GPSTX), TN1.2 (0_RX1_CRX2_CS1)
/MISO: J1.16 (MISO), TN1.14 (12_MISO_MQSL)
/MOSI: J1.15 (MOSI), TN1.13 (11_MOSI_CTX1)
/PTT: R10.2, TN1.35 (13_SCK_LED)
/RCLK: U2.19 (RCLK), U4.9 (CLK2)
/RECV: Q1.2 (C), Q3.2 (G), R8.2, R9.1
/SCL: R2.1, TN1.41 (19_A5_SCL), U1.5 (SCL), U2.17 (SCLK), U4.4 (SCL)
/SDA: R1.1, TN1.40 (18_A4_SDA), U1.4 (SDA), U2.18 (SDIO), U4.5 (SDA)
/X+: J1.9 (X+), TN1.31 (39_MISO1_OUT1A)
/X-: J1.7 (X-), TN1.29 (37_CS), U1.7 (CH2+)
/XCLK: C20.1, U4.13 (CLK0)
/XMIT: C16.2, L3.1, Q2.3 (C), Q4.2 (G), R11.1
/Y+: J1.10 (Y+), TN1.30 (38_CS1_IN1), U1.1 (CH1+)
/Y-: J1.8 (Y-), TN1.28 (36_CS)
GND: BAT1.1, C4.1, C5.1, C7.1, C8.2, C9.2, C10.2, C12.2, C13.2, C14.1, C15.1, C16.1, C17.1, C25.2, C27.1, C28.2, C29.1, D1.1 (K), J1.6 (GND), J1.20 (GND), J2.2 (GND), J3.1 (GND), Q1.1 (E), Q4.1 (S), R3.1, R5.1, R7.1, TN1.1 (GND), TN1.34 (GND), TN1.47 (GND), TN1.52 (GND), U1.2 (CH1-), U1.6 (V_{SS}), U1.8 (CH2-), U2.9 (RFGND), U2.13 (GND), U2.14 (GND), U2.16 (~SEN), U3.2 (GND), U4.7 (OEB), U4.21 (EPAD), Y1.2 (GND)
unnamed: C2.2, C6.1, R3.2
unnamed: C7.2, R4.1, R5.2, R6.1
unnamed: C10.1, C11.2, C19.2, L2.1
unnamed: C19.1, L3.2, U3.3
unnamed: C20.2, U3.1
unnamed: C9.1, C26.1, L1.1, L2.2
unnamed: D1.2 (A), R11.2
unnamed: J1.5 (IM2), J1.18 (3Vo)
unnamed: J1.14 (CS), TN1.12 (10_CS_MQSR)
unnamed: J1.13 (D/C), TN1.11 (9_OUT1C)
unnamed: J1.12 (RST), TN1.10 (8_TX2_IN1)
unnamed: C8.1, C26.2, J2.1 (ANT), L1.2
unnamed: Q1.3 (B), R10.1
unnamed: Q2.2 (B), R8.1
unnamed: C11.1, Q3.3 (D)
unnamed: C3.1, Q3.1 (S), Q4.3 (D), R7.2
unnamed: C6.2, R4.2, TN1.38 (16_A2_RX4_SCL1)
unnamed: TN1.42 (20_A6_TX5_LRCLK1), U2.15 (~RST)
unnamed: BAT1.2, TN1.50 (VBAT)
unnamed: C3.2, U2.12 (AMI)
unnamed: C1.2, U2.22 (DBYP)
unnamed: C2.1, U2.24 (LOUT/[DFS])
unnamed: U4.6 (CLKIN), Y1.3 (OUTPUT)
